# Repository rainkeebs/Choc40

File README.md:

# Choc40
*THIS IS UNTESTED*

These files were made in KiCad nightly. They are not backwards compatible.
40% Low profile keyboard designed for Kailh 'Choc' v1 switches and MBK Extended keycaps.

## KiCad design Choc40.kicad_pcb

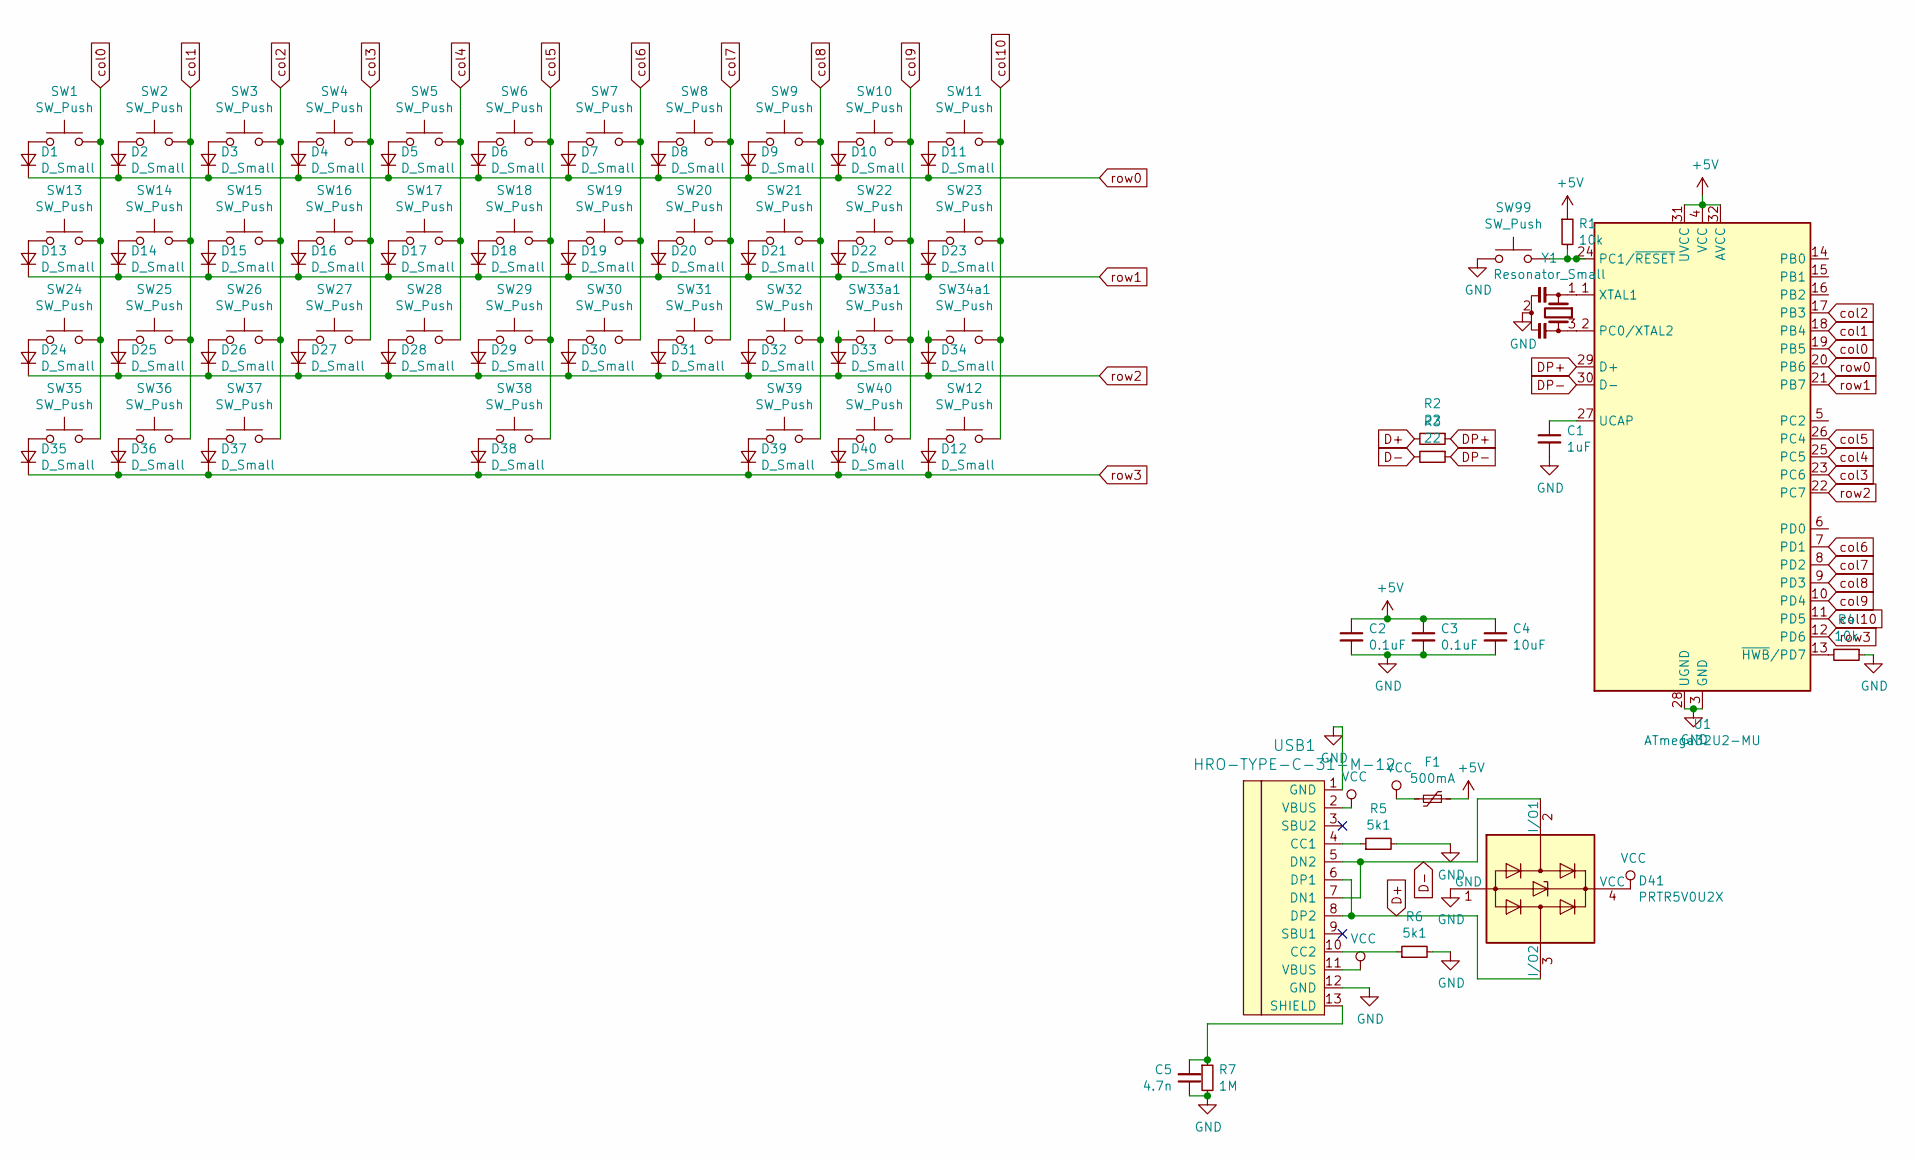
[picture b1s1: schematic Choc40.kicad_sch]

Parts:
C1: 1uF; C_0603_1608Metric
C2, C3: 0.1uF; C_0603_1608Metric
C4: 10uF; C_0603_1608Metric
C5: 4.7n; C_0603_1608Metric
D1, D2, D3, D4, D5, D6, D7, D8, D9, D10, D11, D12, D13, D14, D15, D16, D17, D18, D19, D20, D21, D22, D23, D24, D25, D26, D27, D28, D29, D30, D31, D32, D33, D34, D35, D36, D37, D38, D39, D40: D_Small; D_SOD-123
D41: PRTR5V0U2X; SOT-143
F1: 500mA; Fuse_1206_3216Metric
R1, R4: 10k; R_0603_1608Metric
R2, R3: 22; R_0603_1608Metric
R5, R6: 5k1; R_0603_1608Metric
R7: 1M; R_0603_1608Metric
SW1, SW2, SW3, SW4, SW5, SW6, SW7, SW8, SW9, SW10, SW11, SW12, SW14, SW15, SW16, SW17, SW18, SW19, SW20, SW21, SW22, SW25, SW26, SW27, SW28, SW29, SW30, SW31, SW32, SW33a1, SW36, SW37: SW_Push; Choc-1u-solder
SW13, SW34a1, SW35, SW39, SW40: SW_Push; Choc-1.25u-solder
SW23, SW24: SW_Push; Choc-1.75u-solder
SW38: SW_Push; Choc-6.25u-solder
SW99: SW_Push; SKQG-1155865
U1: ATmega32U2-MU; QFN-32-1EP_5x5mm_P0.5mm_EP3.1x3.1mm
USB1: HRO-TYPE-C-31-M-12
Y1: Resonator_Small; Resonator_SMD_muRata_CSTxExxV-3Pin_3.0x1.1mm

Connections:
+5V: C2.1, C3.1, C4.1, F1.1, R1.1, U1.4 (VCC), U1.31 (UVCC), U1.32 (AVCC)
D+: D41.3 (I/O2), R2.2, USB1.6 (DP1), USB1.8 (DP2)
D-: D41.2 (I/O1), R3.2, USB1.5 (DN2), USB1.7 (DN1)
DP+: R2.1, U1.29 (D+)
DP-: R3.1, U1.30 (D-)
GND: C1.2, C2.2, C3.2, C4.2, C5.1, D41.1 (GND), R4.1, R5.2, R6.2, R7.2, SW99.1, U1.3 (GND), U1.28 (UGND), U1.33 (GND), USB1.1 (GND), USB1.12 (GND), Y1.2
unnamed: C1.1, U1.27 (UCAP)
unnamed: C5.2, R7.1, USB1.13 (SHIELD)
unnamed: D1.2 (A), SW1.1
unnamed: D2.2 (A), SW2.1
unnamed: D3.2 (A), SW3.1
unnamed: D4.2 (A), SW4.1
unnamed: D5.2 (A), SW5.1
unnamed: D6.2 (A), SW6.1
unnamed: D7.2 (A), SW7.1
unnamed: D8.2 (A), SW8.1
unnamed: D9.2 (A), SW9.1
unnamed: D10.2 (A), SW10.1
unnamed: D11.2 (A), SW11.1
unnamed: D12.2 (A), SW12.1
unnamed: D13.2 (A), SW13.1
unnamed: D14.2 (A), SW14.1
unnamed: D15.2 (A), SW15.1
unnamed: D16.2 (A), SW16.1
unnamed: D17.2 (A), SW17.1
unnamed: D18.2 (A), SW18.1
unnamed: D19.2 (A), SW19.1
unnamed: D20.2 (A), SW20.1
unnamed: D21.2 (A), SW21.1
unnamed: D22.2 (A), SW22.1
unnamed: D23.2 (A), SW23.1
unnamed: D24.2 (A), SW24.1
unnamed: D25.2 (A), SW25.1
unnamed: D26.2 (A), SW26.1
unnamed: D27.2 (A), SW27.1
unnamed: D28.2 (A), SW28.1
unnamed: D29.2 (A), SW29.1
unnamed: D30.2 (A), SW30.1
unnamed: D31.2 (A), SW31.1
unnamed: D32.2 (A), SW32.1
unnamed: D33.2 (A), SW33a1.1
unnamed: D34.2 (A), SW34a1.1
unnamed: D35.2 (A), SW35.1
unnamed: D36.2 (A), SW36.1
unnamed: D37.2 (A), SW37.1
unnamed: D38.2 (A), SW38.1
unnamed: D39.2 (A), SW39.1
unnamed: D40.2 (A), SW40.1
unnamed: R1.2, SW99.2, U1.24 (PC1/~RESET)
unnamed: R4.2, U1.13 (~HWB~/PD7)
unnamed: R5.1, USB1.4 (CC1)
unnamed: R6.1, USB1.10 (CC2)
unnamed: U1.1 (XTAL1), Y1.1
unnamed: U1.2 (PC0/XTAL2), Y1.3
VCC: D41.4 (VCC), F1.2, USB1.2 (VBUS), USB1.11 (VBUS)
col0: SW1.2, SW13.2, SW24.2, SW35.2, U1.19 (PB5)
col1: SW2.2, SW14.2, SW25.2, SW36.2, U1.18 (PB4)
col2: SW3.2, SW15.2, SW26.2, SW37.2, U1.17 (PB3)
col3: SW4.2, SW16.2, SW27.2, U1.23 (PC6)
col4: SW5.2, SW17.2, SW28.2, U1.25 (PC5)
col5: SW6.2, SW18.2, SW29.2, SW38.2, U1.26 (PC4)
col6: SW7.2, SW19.2, SW30.2, U1.7 (PD1)
col7: SW8.2, SW20.2, SW31.2, U1.8 (PD2)
col8: SW9.2, SW21.2, SW32.2, SW39.2, U1.9 (PD3)
col9: SW10.2, SW22.2, SW33a1.2, SW40.2, U1.10 (PD4)
col10: SW11.2, SW12.2, SW23.2, SW34a1.2, U1.11 (PD5)
row0: D1.1 (K), D2.1 (K), D3.1 (K), D4.1 (K), D5.1 (K), D6.1 (K), D7.1 (K), D8.1 (K), D9.1 (K), D10.1 (K), D11.1 (K), U1.20 (PB6)
row1: D13.1 (K), D14.1 (K), D15.1 (K), D16.1 (K), D17.1 (K), D18.1 (K), D19.1 (K), D20.1 (K), D21.1 (K), D22.1 (K), D23.1 (K), U1.21 (PB7)
row2: D24.1 (K), D25.1 (K), D26.1 (K), D27.1 (K), D28.1 (K), D29.1 (K), D30.1 (K), D31.1 (K), D32.1 (K), D33.1 (K), D34.1 (K), U1.22 (PC7)
row3: D12.1 (K), D35.1 (K), D36.1 (K), D37.1 (K), D38.1 (K), D39.1 (K), D40.1 (K), U1.12 (PD6)

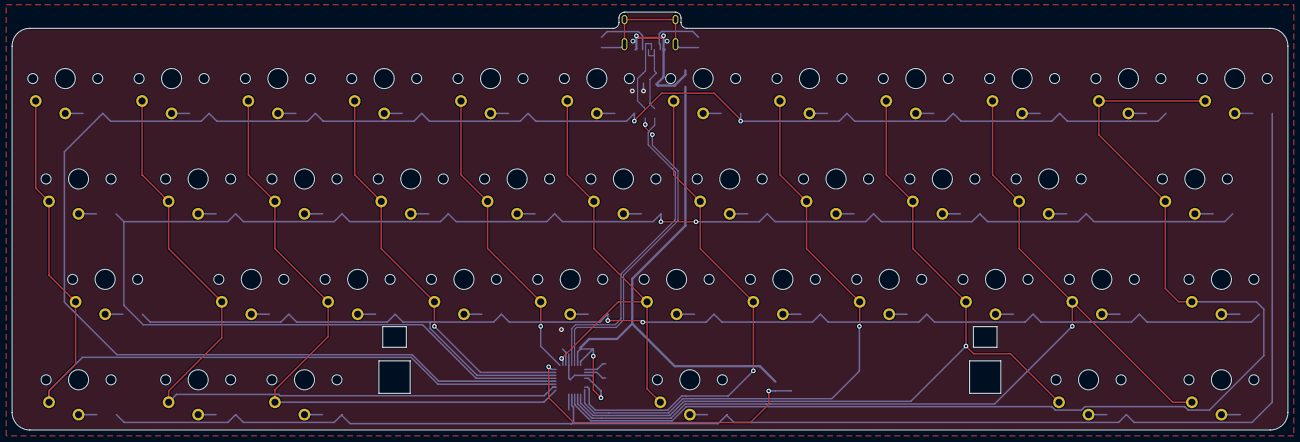
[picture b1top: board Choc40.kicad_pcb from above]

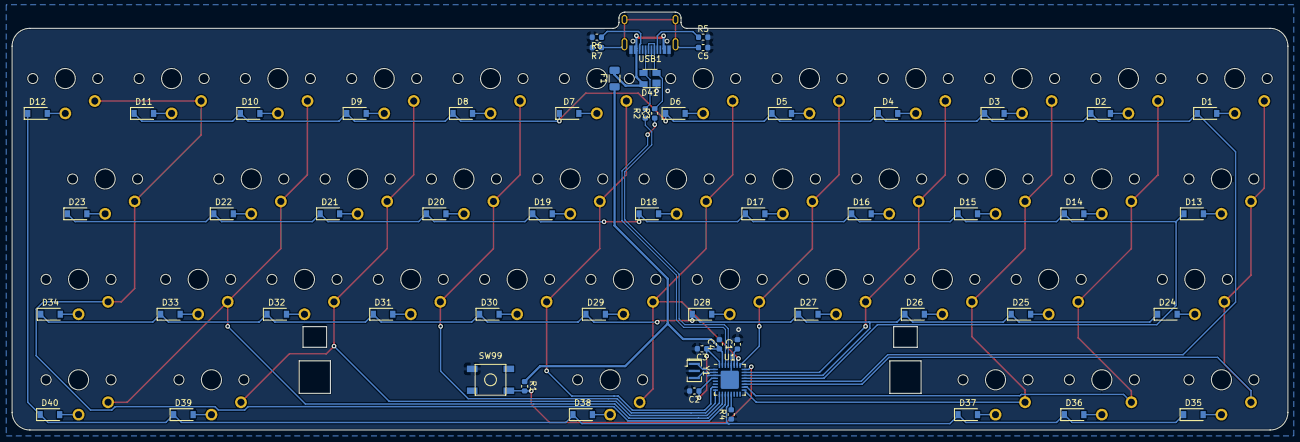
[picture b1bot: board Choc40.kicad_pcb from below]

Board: 2 copper layers, 216.0 x 70.7 mm, 98 parts (58 on the bottom side), 70 nets.

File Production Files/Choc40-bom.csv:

Designator,Qnty,Comment,Cmp name,Footprint,Description,LCSC Part Number,
"C1, ",1,1uF,C_Small,Capacitor_SMD:C_0603_1608Metric,"Unpolarized capacitor, small symbol",,C15849 
"C2, C3, ",2,0.1uF,C_Small,Capacitor_SMD:C_0603_1608Metric,"Unpolarized capacitor, small symbol",,
"C4, ",1,10uF,C_Small,Capacitor_SMD:C_0603_1608Metric,"Unpolarized capacitor, small symbol",,C14663 
"C5, ",1,4.7n,C_Small,Capacitor_SMD:C_0603_1608Metric,"Unpolarized capacitor, small symbol",,C53987 
"D1, D2, D3, D4, D5, D6, D7, D8, D9, D10, D11, D12, D13, D14, D15, D16, D17, D18, D19, D20, D21, D22, D23, D24, D25, D26, D27, D28, D29, D30, D31, D32, D33, D34, D35, D36, D37, D38, D39, D40, ",40,D_Small,D_Small,Diode_SMD:D_SOD-123,"Diode, small symbol",,C524051 
"D41, ",1,PRTR5V0U2X,PRTR5V0U2X,Package_TO_SOT_SMD:SOT-143,"Ultra low capacitance double rail-to-rail ESD protection diode, SOT-363",,C384891 
"F1, ",1,500mA,Polyfuse_Small,Fuse:Fuse_1206_3216Metric,"Resettable fuse, polymeric positive temperature coefficient, small symbol",,C70076 
"R1, R4, ",2,10k,R_Small,Resistor_SMD:R_0603_1608Metric,"Resistor, small symbol",,C25804 
"R2, R3, ",2,22,R_Small,Resistor_SMD:R_0603_1608Metric,"Resistor, small symbol",,C23345 
"R5, R6, ",2,5k1,R_Small,Resistor_SMD:R_0603_1608Metric,"Resistor, small symbol",,C23186 
"R7, ",1,1M,R_Small,Resistor_SMD:R_0603_1608Metric,"Resistor, small symbol",,C22935 
"U1, ",1,ATmega32U2-MU,ATmega32U2-MU,Package_DFN_QFN:QFN-32-1EP_5x5mm_P0.5mm_EP3.1x3.1mm,"16MHz, 32kB Flash, 1kB SRAM, 1kB EEPROM, QFN-32",,C57345 
"USB1, ",1,HRO-TYPE-C-31-M-12,HRO-TYPE-C-31-M-12,Type-C:HRO-TYPE-C-31-M-12,,,C165948 
"Y1, ",1,Resonator_Small,Resonator_Small,Crystal:Resonator_SMD_muRata_CSTxExxV-3Pin_3.0x1.1mm,"Three pin ceramic resonator, small symbol",,C341521

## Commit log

2021-03-22 Added mbk_footprints submodule
    https://github.com/nicoles/mbk_footprints.git
2021-03-22 Added Type C.pretty
    https://github.com/ai03-2725/Type-C.pretty.git
2021-03-22 pcb go brr
2021-03-22 Create LICENSE
    change to Unlicense
2021-03-22 le epic progression
2021-03-23 PCB finished
2021-03-23 Schematic finished
2021-03-24 switcvh plate
2021-03-24 Production files added
2021-03-24 bom fix
